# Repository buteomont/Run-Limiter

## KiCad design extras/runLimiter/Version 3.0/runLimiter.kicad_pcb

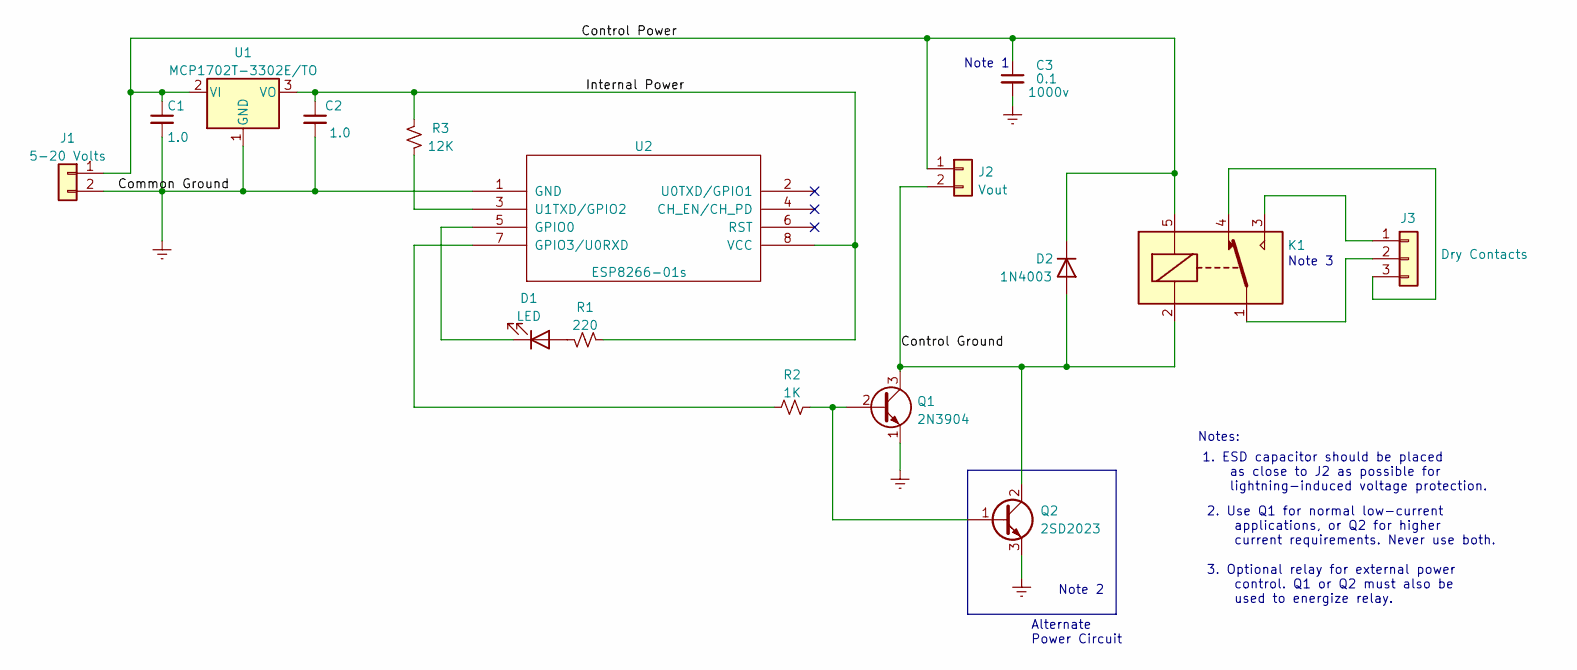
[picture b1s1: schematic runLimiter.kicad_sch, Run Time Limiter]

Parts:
C1, C2: 1.0; CP_Radial_Tantal_D4.5mm_P2.50mm
C3: 0.1; C_Disc_D10.5mm_W5.0mm_P10.00mm; Rating 1000v
D1: LED; LED_D5.0mm
D2: 1N4003; D_DO-41_SOD81_P10.16mm_Horizontal
J1: 5-20 Volts; PinHeader_1x02_P2.54mm_Vertical
J2: Vout; PinHeader_1x02_P2.54mm_Vertical
J3: Dry Contacts; PinHeader_1x03_P2.54mm_Vertical
K1: Relay; Relay_SPDT_SANYOU_SRD_Series_Form_C
Q1: 2N3904; TO-92_Inline
Q2: 2SD2023; TO-220-3_Vertical
R1: 220; R_Axial_DIN0207_L6.3mm_D2.5mm_P10.16mm_Horizontal
R2: 1K; R_Axial_DIN0207_L6.3mm_D2.5mm_P10.16mm_Horizontal
R3: 12K; R_Axial_DIN0207_L6.3mm_D2.5mm_P10.16mm_Horizontal
U1: MCP1702T-3302E/TO; TO-92_Inline
U2: ESP8266-01s

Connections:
/Control Ground: D2.2 (A), J2.2, K1.2, Q1.3 (C), Q2.2 (C)
/Control Power: C1.1, C3.1, D2.1 (K), J1.1, J2.1, K1.5, U1.2 (VI)
/Internal Power: C2.1, R1.2, R3.2, U1.3 (VO), U2.8 (VCC)
GNDREF: C1.2, C2.2, C3.2, J1.2, Q1.1 (E), Q2.3 (E), U1.1 (GND), U2.1 (GND)
unnamed: D1.1 (K), U2.5 (GPIO0)
unnamed: D1.2 (A), R1.1
unnamed: J3.2, K1.1
unnamed: J3.1, K1.3
unnamed: J3.3, K1.4
unnamed: Q1.2 (B), Q2.1 (B), R2.1
unnamed: R2.2, U2.7 (GPIO3/U0RXD)
unnamed: R3.1, U2.3 (U1TXD/GPIO2)

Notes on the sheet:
Note 3
Notes:
3. Optional relay for external power control. Q1 or Q2 must also be used to energize relay.
1. ESD capacitor should be placed as close to J2 as possible for lightning-induced voltage protection.
Alternate Power Circuit
Note 1
Note 2
2. Use Q1 for normal low-current applications, or Q2 for higher current requirements. Never use both.

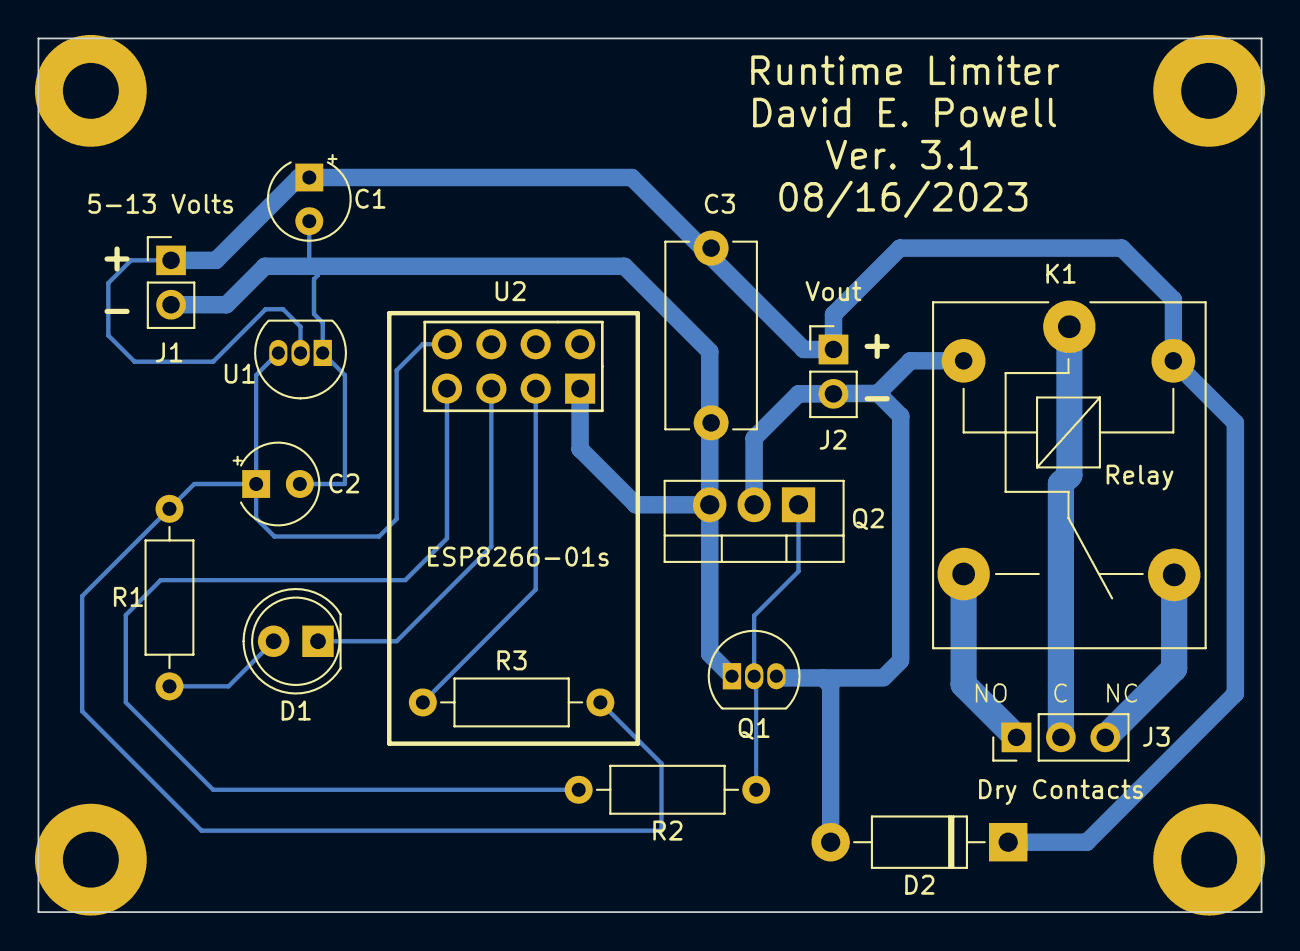
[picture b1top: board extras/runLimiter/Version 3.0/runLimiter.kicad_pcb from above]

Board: 2 copper layers, 70.0 x 50.0 mm, 16 parts (0 on the bottom side), 12 nets.

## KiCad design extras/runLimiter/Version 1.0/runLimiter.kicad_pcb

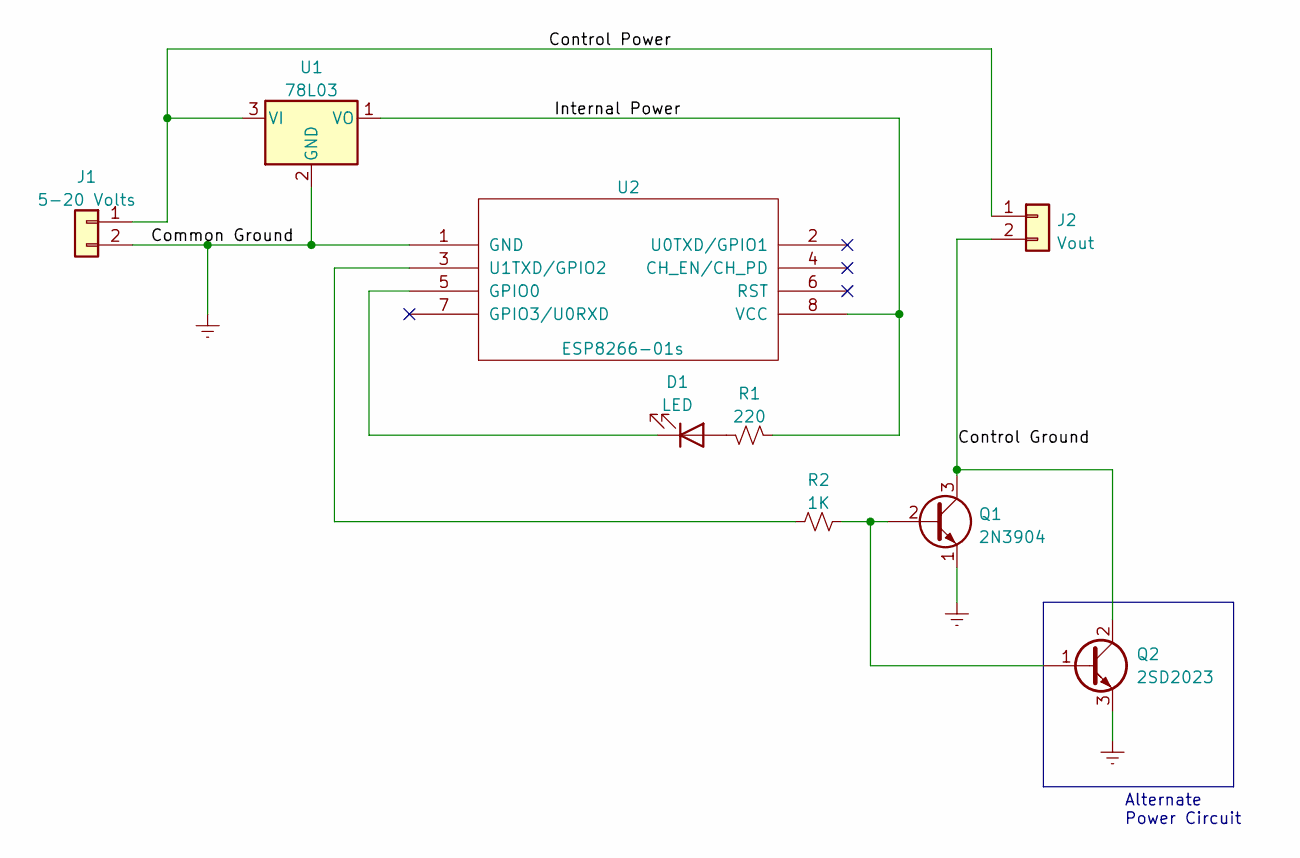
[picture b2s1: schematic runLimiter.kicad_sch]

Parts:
D1: LED; LED_D5.0mm
J1: 5-20 Volts; PinHeader_1x02_P2.54mm_Vertical
J2: Vout; PinHeader_1x02_P2.54mm_Vertical
Q1: 2N3904; TO-92_Inline
Q2: 2SD2023; TO-220-3_Vertical
R1: 220; R_Axial_DIN0207_L6.3mm_D2.5mm_P10.16mm_Horizontal
R2: 1K; R_Axial_DIN0207_L6.3mm_D2.5mm_P10.16mm_Horizontal
U1: 78L03; TO-92_Inline
U2: ESP8266-01s

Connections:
/Control Ground: J2.2, Q1.3 (C), Q2.2 (C)
/Control Power: J1.1, J2.1, U1.3 (VI)
/Internal Power: R1.2, U1.1 (VO), U2.8 (VCC)
GNDREF: J1.2, Q1.1 (E), Q2.3 (E), U1.2 (GND), U2.1 (GND)
unnamed: D1.1 (K), U2.5 (GPIO0)
unnamed: D1.2 (A), R1.1
unnamed: Q1.2 (B), Q2.1 (B), R2.1
unnamed: R2.2, U2.3 (U1TXD/GPIO2)

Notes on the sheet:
Alternate Power Circuit

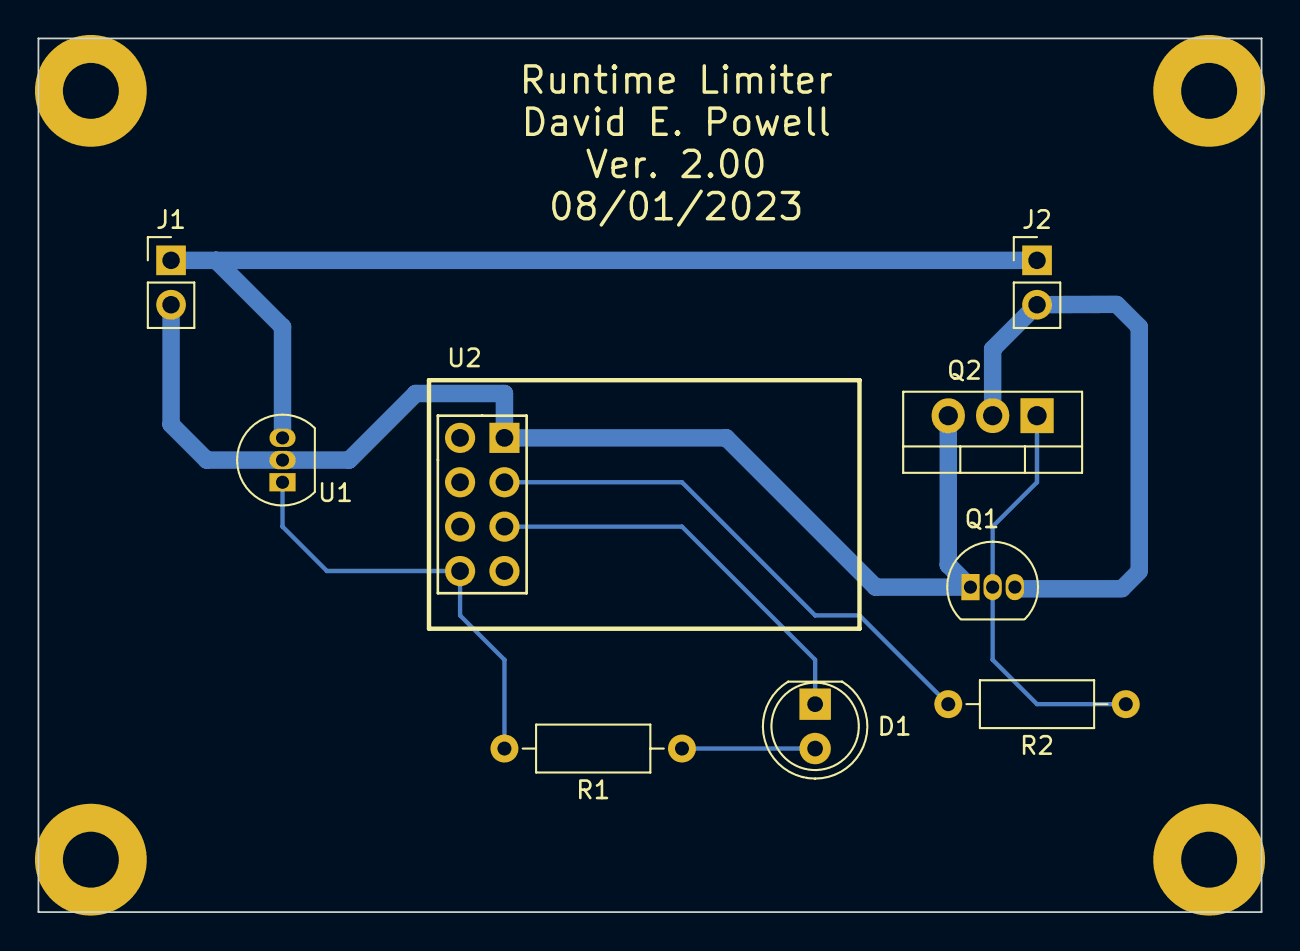
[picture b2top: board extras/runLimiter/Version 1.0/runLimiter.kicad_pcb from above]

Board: 2 copper layers, 70.0 x 50.0 mm, 9 parts (0 on the bottom side), 8 nets.

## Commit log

2021-07-03 Added OTA update feature
2021-07-03 Added schematic
2021-07-17 Moved timeout LED to port D2
2021-07-18 Updated schematic
2021-12-26 Added schematic and note about water pump
2022-04-09 Added protection capacitor to output Added feedback divider for output verification
2022-04-09 Minor update
2023-06-20 Added support to enable and disable flashing LED
2023-06-20 Exported images of schematics
2023-06-20 Fixed settings carriage return bug
2023-06-20 Minor cleanup
2023-07-10 PC board files
2023-08-08 Modified directory structure
2023-08-16 Moved power control from GPIO2 to GPIO3
2023-08-16 Refactored files, replaced C1, C2 footprints
2023-08-16 Updated version number on silkscreen
2023-08-17 Updated some comments
2023-08-17 Changes to board and schematic
2023-09-07 Added PRECONFIGURE #define for to enable serial
2026-05-01 fixed some syntax that was generating warnings
